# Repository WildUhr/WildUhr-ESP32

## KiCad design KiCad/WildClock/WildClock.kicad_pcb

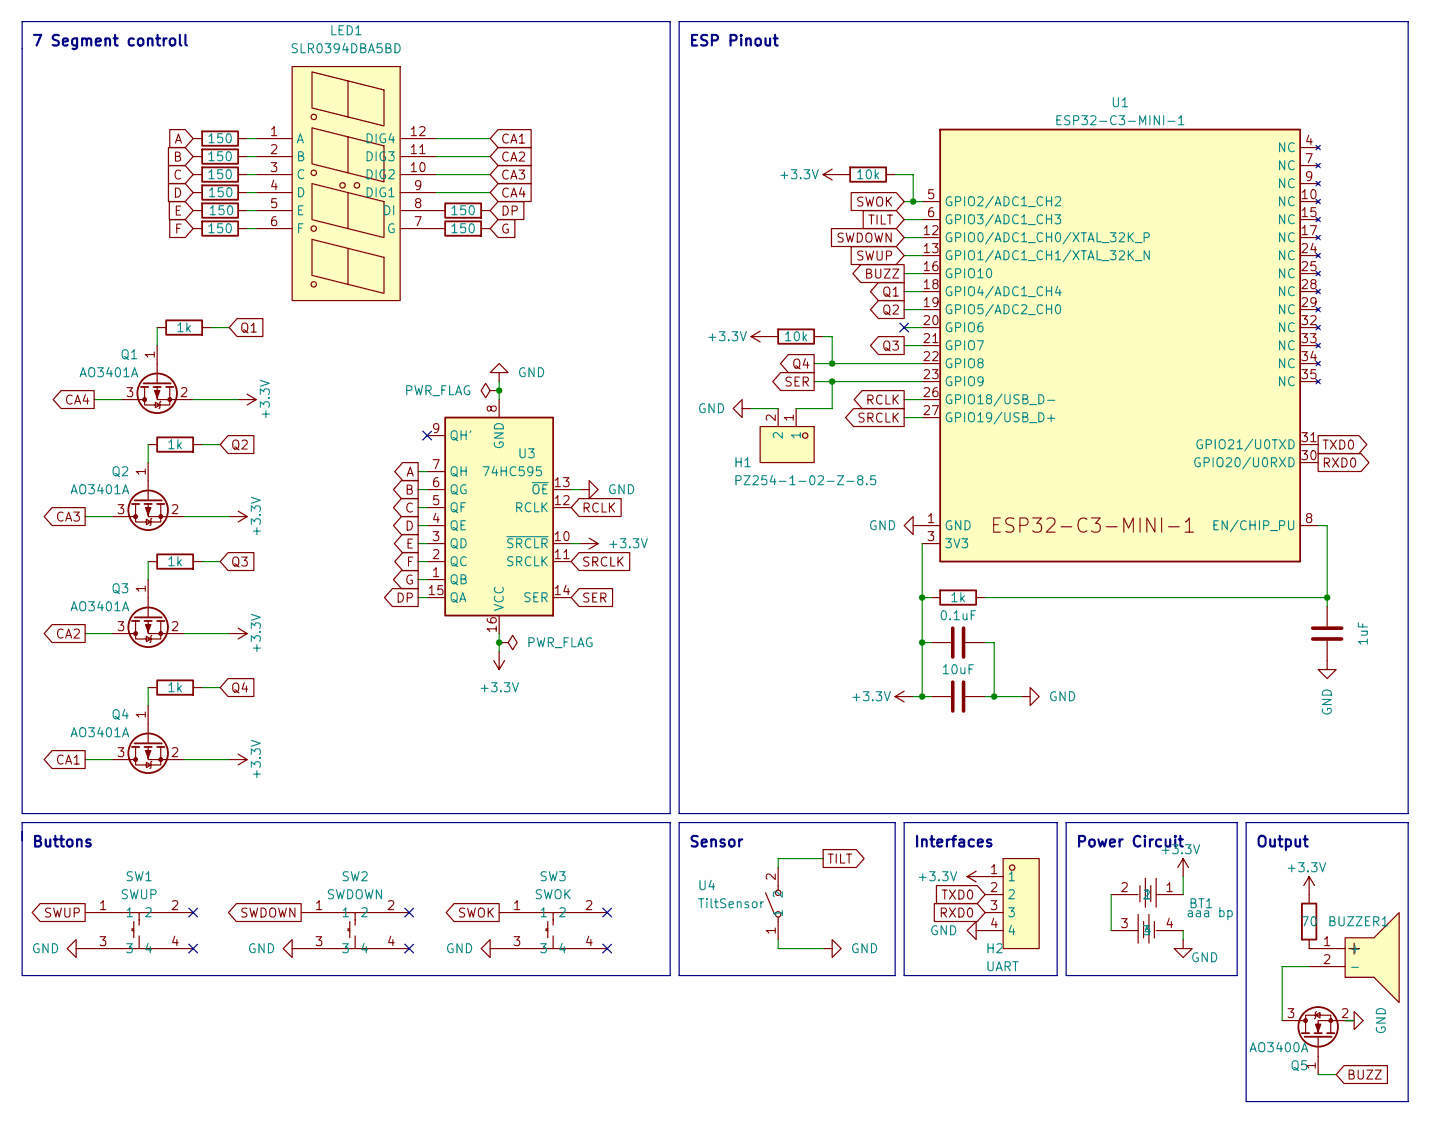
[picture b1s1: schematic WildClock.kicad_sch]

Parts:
BT1: aaa bp; BAT-SMD_BH-AAA-B5AA001; LCSC Part C964881
BUZZER1: GMC1209YB-25R2048; BUZ-TH_BD12.0-P6.50-D0.6-FD; LCSC Part C252921
C1: 10uF; C_0805_2012Metric
C2: 0.1uF; C_0805_2012Metric
C3: 1uF; C_0805_2012Metric
H1: PZ254-1-02-Z-8.5; HDR-TH_2P-P2.54-V-M; LCSC Part C2894925
H2: UART; HDR-TH_4P-P2.54-V-M; LCSC Part C2894927
LED1: SLR0394DBA5BD; LED-SEG-TH_SLR0394DBA5BD; LCSC Part C225903
Q1, Q2, Q3, Q4: AO3401A; SOT-23
Q5: AO3400A; SOT-23
R1, R3, R4, R5, R15: 1k; R_0805_2012Metric
R2: 70; R_0805_2012Metric
R6, R16: 10k; R_0805_2012Metric
R7, R8, R9, R10, R11, R12, R13, R14: 150; R_0805_2012Metric
SW1: SWUP; SW-TH_4P-L6.0-W6.0-P4.50-LS6.5; LCSC Part C455102
SW2: SWDOWN; SW-TH_4P-L6.0-W6.0-P4.50-LS6.5; LCSC Part C455102
SW3: SWOK; SW-TH_4P-L6.0-W6.0-P4.50-LS6.5; LCSC Part C455102
U1: ESP32-C3-MINI-1
U3: 74HC595; SOIC-16_L9.9-W3.9-P1.27-LS6.0-BL
U4: TiltSensor; SENSOR-TH_SW-520DS-AB12G; LCSC Part C2905288

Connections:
+3.3V: BT1.1, C1.2, C2.2, H2.1, Q1.2 (S), Q2.2 (S), Q3.2 (S), Q4.2 (S), R2.1, R6.2, R15.2, R16.2, U1.3 (3V3), U3.10 (~SRCLR), U3.16 (VCC)
A: R7.2, U3.7 (QH)
B: R8.2, U3.6 (QG)
BUZZ: Q5.1 (G), U1.16 (GPIO10)
C: R9.2, U3.5 (QF)
CA1: LED1.12 (DIG4), Q4.3 (D)
CA2: LED1.11 (DIG3), Q3.3 (D)
CA3: LED1.10 (DIG2), Q2.3 (D)
CA4: LED1.9 (DIG1), Q1.3 (D)
D: R10.2, U3.4 (QE)
DP: R14.2, U3.15 (QA)
E: R11.2, U3.3 (QD)
F: R12.2, U3.2 (QC)
G: R13.2, U3.1 (QB)
GND: BT1.4, C1.1, C2.1, C3.1, H1.2, H2.4, Q5.2 (S), SW1.3, SW2.3, SW3.3, U1.1 (GND), U1.2 (GND), U1.36 (GND), U1.37 (GND), U1.38 (GND), U1.39 (GND), U1.40 (GND), U1.41 (GND), U1.42 (GND), U1.43 (GND), U1.44 (GND), U1.45 (GND), U1.46 (GND), U1.47 (GND), U1.48 (GND), U1.49 (GND), U1.50 (GND), U1.51 (GND), U1.52 (GND), U1.53 (GND), U3.8 (GND), U3.13 (~OE), U4.1
unnamed: BT1.2, BT1.3
unnamed: BUZZER1.1 (+), R2.2
unnamed: BUZZER1.2 (-), Q5.3 (D)
unnamed: LED1.1 (A), R7.1
unnamed: LED1.2 (B), R8.1
unnamed: LED1.3 (C), R9.1
unnamed: LED1.4 (D), R10.1
unnamed: LED1.8 (DI), R14.1
unnamed: LED1.5 (E), R11.1
unnamed: LED1.6 (F), R12.1
unnamed: LED1.7 (G), R13.1
unnamed: Q1.1 (G), R1.1
unnamed: Q2.1 (G), R3.1
unnamed: Q3.1 (G), R4.1
unnamed: Q4.1 (G), R5.1
unnamed: C3.2, R15.1, U1.8 (EN/CHIP_PU)
Q1: R1.2, U1.18 (GPIO4/ADC1_CH4)
Q2: R3.2, U1.19 (GPIO5/ADC2_CH0)
Q3: R4.2, U1.21 (GPIO7)
Q4: R5.2, R6.1, U1.22 (GPIO8)
RCLK: U1.26 (GPIO18/USB_D-), U3.12 (RCLK)
RXD0: H2.3, U1.30 (GPIO20/U0RXD)
SER: H1.1, U1.23 (GPIO9), U3.14 (SER)
SRCLK: U1.27 (GPIO19/USB_D+), U3.11 (SRCLK)
SWDOWN: SW2.1, U1.12 (GPIO0/ADC1_CH0/XTAL_32K_P)
SWOK: R16.1, SW3.1, U1.5 (GPIO2/ADC1_CH2)
SWUP: SW1.1, U1.13 (GPIO1/ADC1_CH1/XTAL_32K_N)
TILT: U1.6 (GPIO3/ADC1_CH3), U4.2
TXD0: H2.2, U1.31 (GPIO21/U0TXD)

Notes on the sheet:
ESP Pinout
Power Circuit
Buttons
7 Segment controll
Output
Interfaces
Sensor

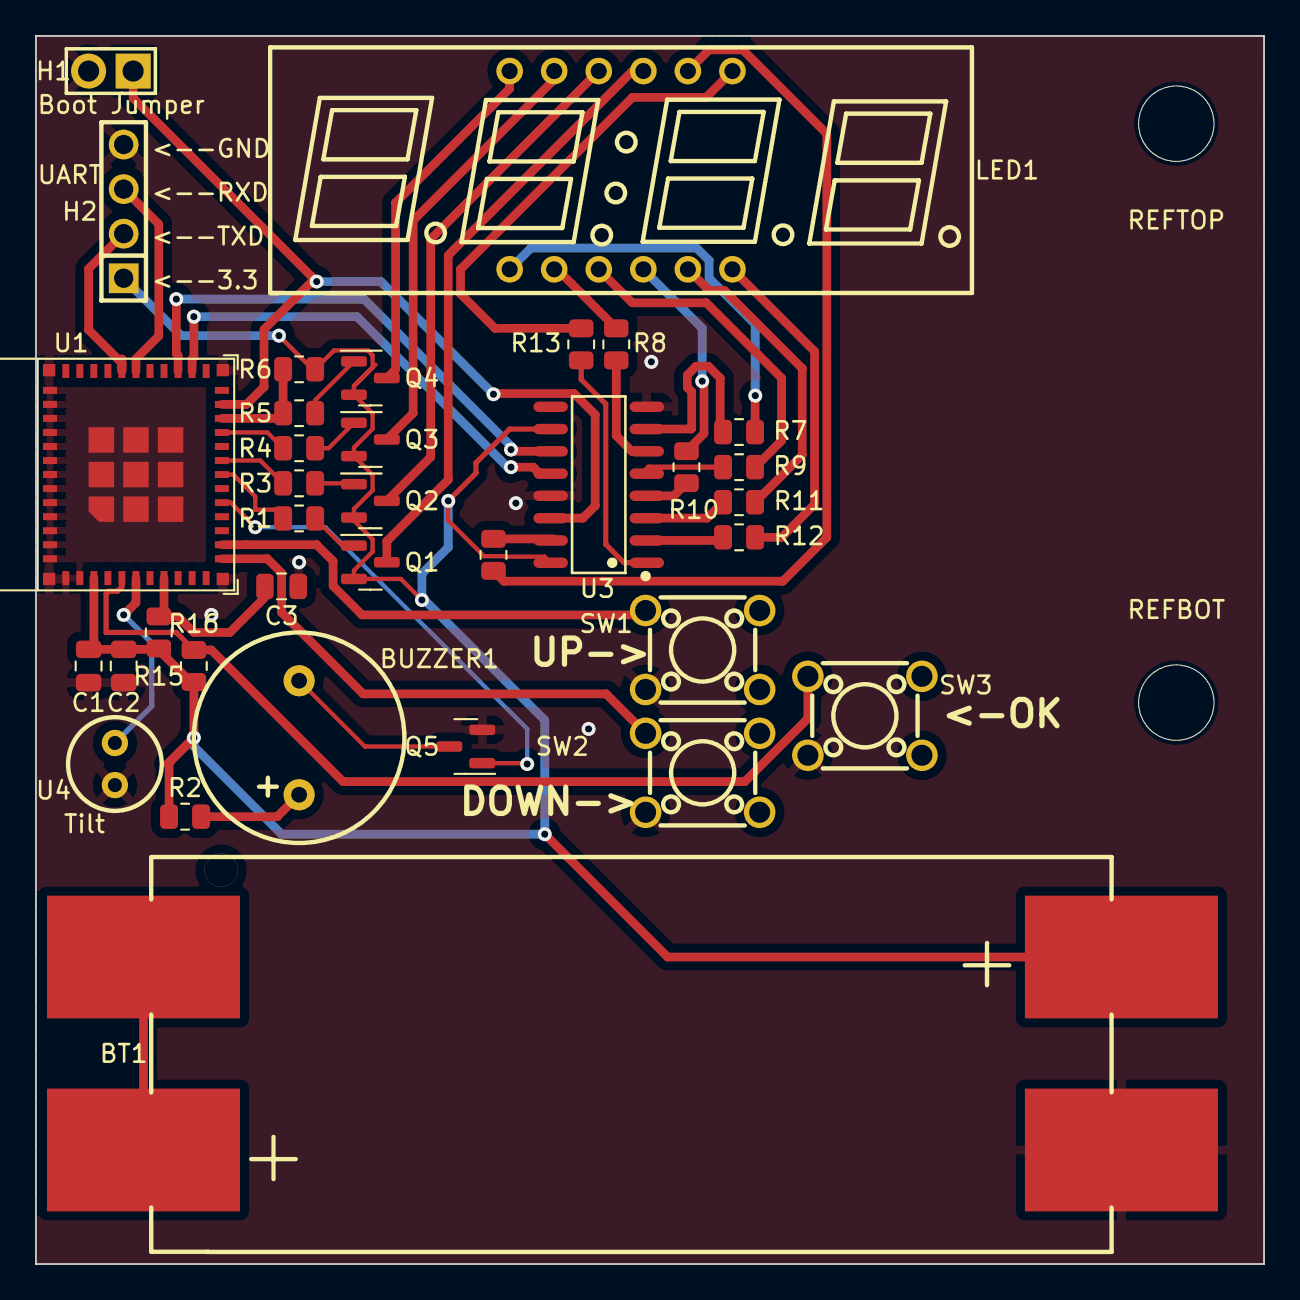
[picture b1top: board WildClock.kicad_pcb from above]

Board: 2 copper layers, 70.0 x 70.0 mm, 37 parts (0 on the bottom side), 44 nets.

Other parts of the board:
REFBOT: MountingHole_4.3mm_M4
REFTOP: MountingHole_4.3mm_M4

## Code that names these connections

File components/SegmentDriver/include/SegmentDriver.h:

#ifndef SEGMENT_DRIVER_H
#define SEGMENT_DRIVER_H

#include <stdio.h>
#include "driver/gpio.h"
#include "DisplayTime.h"
#include "esp_timer.h"

#define RCLK GPIO_NUM_18
#define SRCLK GPIO_NUM_19
#define SER GPIO_NUM_9
#define CA1 GPIO_NUM_4
#define CA2 GPIO_NUM_5
#define CA3 GPIO_NUM_7
#define CA4 GPIO_NUM_8
//      
//          8
//       -------
//    3 |       | 7
//      |   2   |
//       -------
//    4 |       | 6
//      |       |    1
//       -------   .
//          5
//      
#define DIGIT_0 0b00111111
#define DIGIT_1 0b00000110
#define DIGIT_2 0b01011011
#define DIGIT_3 0b01001111
#define DIGIT_4 0b01100110
#define DIGIT_5 0b01101101
#define DIGIT_6 0b01111101
#define DIGIT_7 0b00000111
#define DIGIT_8 0b01111111
#define DIGIT_9 0b01101111
//                      12345678
#define DIGIT_UNKNOWN 0b01000000
class SegmentDriver
{
private:
    DisplayTime time = { 0, 0 };
    esp_timer_handle_t cycleDigitsTimerHandle;
    esp_timer_handle_t blinkTimerHandle;
    esp_timer_handle_t blinkDigitTimerHandle;

    int digitCount = 0;
    int testDigit = -1;
    int digitToBlink = 0;
    bool showPoints = false;
    bool showBlinkDigit = false;
    bool showDash = false;
    bool panic = false;
public:
private:
    void InitTimer();
    void InitGpio();
    void FillRegister();
    void FlashSegments();
    void ClearSegments();
    int GetCurrentDigitFromTime();
    int GetDigitBitmask(int digit);

public:
    SegmentDriver(/* args */) {};
    ~SegmentDriver() {};
    void Init();
    void UpdateTime(DisplayTime* time);
    void NextDigit();
    void Blink();
    void ToggleBlink();
    void ToggleDash();
    bool IsInPanicMode();
    void ReadyForSleep();
    void BlinkOnlyDigit(int digit);
    void BlinkDigit();
    void StopBlinkOnlyDigit();  
};

#endif

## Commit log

2023-01-17 remove all prints and switch to logging
2023-01-21 add own logging
2023-01-25 migrate to esp-c3
2023-02-21 added kicad files
2023-02-22 make all clearer and neu pcb
2023-02-23 changed some footprints
2023-02-27 start updating footprints to match jlcpcb
2023-03-04 use lcsc footprints
2023-03-27 implemented maxis changes
2023-03-27 added lables and move everything closer together
2023-03-27 fix batterie orientation
2023-09-22 redo tcp debugger and clean up
2023-09-22 format files
2023-09-22 remove kicad files
2023-09-23 remove kicad from gitignore
2023-09-25 add segment logging and new macro
2023-09-28 Working display
2023-09-28 add Blinking
2023-09-28 preatier blink and add logging
2023-09-29 first button draft
2023-10-03 add kernel and button debounce
2023-10-03 arm and navigate controll
2023-10-04 update documentation
2023-10-05 implement menue
2023-10-07 implement armed state and improve vis
2023-10-07 not working armed
2023-10-08 add initial sleep
2023-10-08 readz to sleep
2023-10-10 fliped tilt sensor and fixed deep sleep and nvs state recovery
2023-10-12 cleanup and save state
2023-10-12 quick fix button bug
2023-10-12 massive code cleanup and watchdog fix
2023-10-16 add button sleep
2023-10-17 better Time set methode
2023-10-17 add inactive sleep
2023-10-18 fix wait wake up
2023-11-02 update controll diagramm
